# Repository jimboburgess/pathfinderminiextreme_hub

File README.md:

HERE ARE FILES FOR CREATING A SIMPLE PATHFINDER BASED GAME.

Multiplayer Stage 1 architecture and audit: `docs/multiplayer-stage1.md`

Multiplayer Stage 2 exploration implementation: `docs/multiplayer-stage2.md`

Cross-platform migration plan: `docs/CROSS_PLATFORM_MIGRATION.md`

Native portable-leaf build and tests: `docs/NATIVE_BUILD.md`

IT RUNS ON AN ESP32-S3-ZERO ON A 240 X 240 TFT SCREEN.

AS ON 7/6/20206 IT IS PROGRAMMED TO RUN ON two BUTTONS, and an ec11 encoder
this is not an image of the game as it stands, the pokemon style battles have been removed and replaced by a tactical grid based battle system. 

These are the parts you'll need or something similar.
I am using an 

ESP32-s3-zero

two simple buttons
A24 Round Tactile Button Caps

EC11 analog encoder

a piezo transducer

a 240x240 tft screen

also, if you want if portable add a battery and charging module

here are the pinouts used in version 0.22
// Display

#define TFT_SCL   12

#define TFT_SDA   11

#define TFT_RST   7

#define TFT_DC    9

#define TFT_CS    10

#define TFT_BL    8

// Encoder

#define ENCODER_CLK      1

#define ENCODER_DT       2

#define ENCODER_SW       3

// Buttons

#define BUTTON_A         4

#define BUTTON_B         5

//piezo

#define PIEZO_PIN 6

The eventual plan is to have a small RPG.

Character select
  
  Fighter
  
  Arcane Spell caster
  
  Rogue
  
  Cleric

Town
  Home, for rest
  
  Ye olde shoppe, for selling a buying gear and potions
  
  Castle, for accepting simple quests such as kill 10 goblins, find 200ft of rope, etc. 
  
  Barn, for chicken looking or horse peepin.
  
  perhaps othr characters to talk with.

Dungeons

  using the five room dungeon technique
  https://donjon.bin.sh/fantasy/5_room/

  Entrance and Guardian: An initial challenge or obstacle that establishes the dungeon's theme and keeps casual looters out.
  
  Puzzle or Roleplaying Challenge: A mental or social trial that provides a change of pace from straight combat.
  
  Trick or Setback: A trap, red herring, or unexpected complication designed to build tension.
  
  Climax, Big Battle, or Conflict: The major boss fight or final confrontation of the adventure.
  
  Reward, Revelation, or Plot Twist: The resolution, where the players receive their loot, discover a secret.

  Eventually, One player can join with other players to complete dungeons. using ESP NOW connections.

Add more type of enemies

goblins

oozes

undead skeleton, necromancer, spirits

demons/devils

elementals or giants

classic beasts i.e. owlbear

dragons

  main.ino
│
├── setup()
├── loop()

buttons.ino

├── handleButtons()

├── handleStartButtons()

├── handleBattleButtons()

└── handleEndScreenButtons()

│
battle.ino
│
├── performAttack()

├── takePlayerTurn()

├── takeEnemyTurn()

├── useHealingPotion()

├── defend()

├── runAway()

└── resetBattle()

│
display.ino
│

├── drawStartScreen()

├── drawStartAnimation()

├── drawBattleScreen()

├── drawBattleSprites()

└── drawCriticalHit()

│
enemies.ino
│

└── generateGoblin()
│

potions.ino
│

└── usePotion()
│

sprites.cpp

sprites.h

characters.h

battle.h

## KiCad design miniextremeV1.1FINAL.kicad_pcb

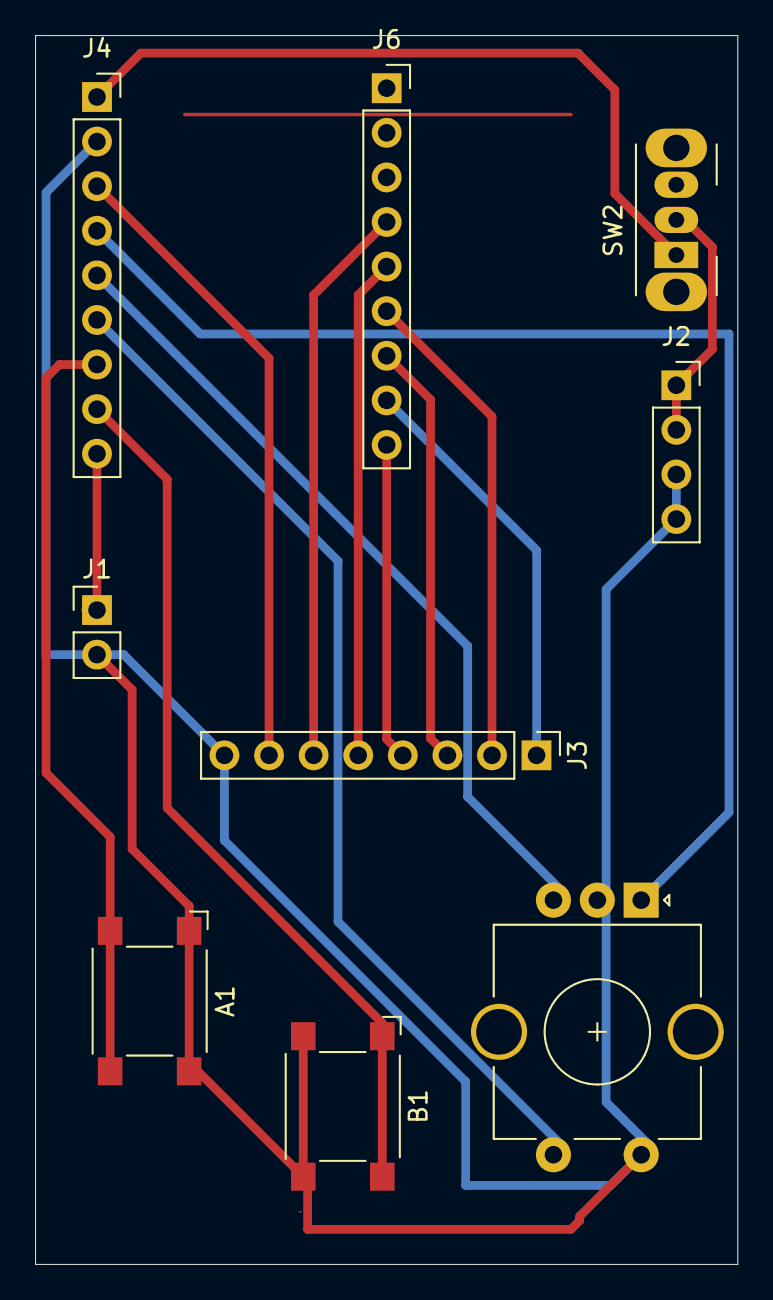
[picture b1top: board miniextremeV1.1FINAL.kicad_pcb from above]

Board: 2 copper layers, 40.0 x 70.0 mm, 9 parts (0 on the bottom side), 16 nets.

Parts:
A1: B3FS-1050; SW_SPST_Omron_B3FS-100xP
B1: B3FS-1050; SW_SPST_Omron_B3FS-100xP
J1: PIEZO; PinHeader_1x02_P2.54mm_Vertical
J2: POWER; PinSocket_1x04_P2.54mm_Vertical
J3: TFT DIsplay; PinHeader_1x08_P2.54mm_Vertical
J4: ESP32-S3-1; PinSocket_1x09_P2.54mm_Vertical
J6: ESP32-S3-2; PinSocket_1x09_P2.54mm_Vertical
SW1: RotaryEncoder_Switch_EC11; RotaryEncoder_Alps_EC11E-Switch_Vertical_H20mm_CircularMoun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
SW2: POWER; SW_Slide_SPDT_Angled_CK_OS102011MA1Q

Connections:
+3.3V: J3.7, J4.3
+5V: J4.1, SW2.1 (A)
ABTN: A1.2, J4.7
A/CLK: J4.4, SW1.A
BBTN: B1.1, J4.8
B/DT: J4.5, SW1.B
EC_SW: J4.6, SW1.S1
GND: A1.1, B1.2, J1.2, J2.3, J2.4, J3.8, J4.2, SW1.C, SW1.S2
unnamed: J1.1, J4.9
unnamed: J2.1, J2.2, SW2.2 (B)
TFT BL: J3.1, J6.8
TFT CS: J3.2, J6.6
TFT DC: J3.3, J6.7
TFT RST: J3.4, J6.9
TFT SCL: J3.6, J6.4
TFT SDA: J3.5, J6.5
